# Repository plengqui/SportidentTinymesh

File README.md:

# Sportident online control using Tinymesh 169Mhz radio
A forest-optimized, reliable mesh radio for Sportident with up to 1,5km per hop.
This document introduces the project idea and product vision on a high level.
# Project context and background
In orienteering and other outdoor sports, the [Sportident](https://www.sportident.com/) system is often used to electronically register when a participant passes a checkpoint. One drawback of Sportident is that the checkpoint pass time registrations cannot be read out until the participant has finished the course. In order to make sports using the Sportident system more exciting for the audience, there is a need for real-time communication from the checkpoints to the competition administration at the arena. A number of solutions already exist for this, such as the excellent [Radio Online Control](http://olresultat.se/), current loop signaling over military [telephone wire](http://hem.bredband.net/sunjo/index.htm), [jSh Radio](http://radio.jsh.de/), etc. While they each have their advantages, most solutions are a bit bulky which makes it burdensome to deploy more than a couple of online checkpoints in each race. For solutions that rely on mobile data networks, there is also the risk at big competitions that the network becomes overloaded on competition day by the large number of runners and viewers appearing on the arena, which is typically a location where mobile networks are not dimensioned for such high load. 
# Product vision
This project aims to produce a neat lightweight radio solution that is easy to deploy in forest conditions, while being very reliable in terms of delivering 100% of punches to the arena in all possible weather conditions. The finished product is a radio unit - a small box about the size of a fist - which is directly attached to a flexible 130 cm roll-up antenna. The antenna + radio unit can hang from a tree anywhere within 8m from the Sportident units at the control. No cabling is needed on the ground. No calibration of directional antennas is needed.
About 10 radio units including antennas can be carried in a backpack and easily deployed by one person with very limited technical knowledge. 
# Technologies used
## Tinymesh
The radio units communicate using a widely used and well supported mesh radio protocol from Radiocrafts called Tinymesh. They use the 169 MHz band, which implies wavelengths of almost 2 meters. Thus they have very good propagation even through dense and wet forest. Distances of 1,5 km per hop have been tested with continuous operation through hilly forest with 500mW effect and Slim Jim antennas. Tinymesh is a self-configuring, self-healing, monitorable mesh technology, implemented in a small surface-mounted component containing both transceiver and protocol logic.
Nodes in a Tinymesh network can be of two types: Router or Gateway. There is only one Gateway per network. All serial data sent from Rounters are automatically routed to the Gateway.
The [Tinymesh datasheet](docs/RCxxxxHP-TM_Data_Sheet.pdf) from Radiocrafts contains everything we need to know in this project, from an overview of the solution to detailed explanation of the protocol and packet formats. I have highlighted the parts of the datasheet that are relevant to this project and added some annotations. The specific module we use is RC1701(HP)-TM, whose default operating frequency is 169.40625 MHz with max effect of 500mW.
This radio band is unlicensed in most european countries, including [Sweden](https://www.pts.se/sv/Bransch/Radio/Radiotillstand/Undantag-fran-tillstandsplikt/):
>88 § 169,400–169,475 MHz: Radiosändare för ospecificerat tillämpningsområde. Högsta effekt: 500 mW e.r.p. Kanaldelning: Upp till 50 kHz. Sändningscykel: < 1 %

>89 § 169,400–169,475 MHz: Radiosändare för mätutrustning. Högsta effekt: 500 mW e.r.p. Kanaldelning: Upp till 50 kHz. Sändningscykel: < 10 %.

## Slim Jim antenna

The Slim Jim antenna is perfect for this application, being easy to transport rolled up, and quick to deploy by just hanging it from a tree nearby, up to 8m from the Sportident station. The antenna is 130 cm long, and the small Radio Unit box can be attached diretly at the lower end of the antenna. 

## Sportident Short Range Radio (SRR)
The Sportident units at the control are [SRR](https://www.sportident.com/images/PDF/1_si_base_products/8_si-radio/SRR-Kit/SPORTident_SRR_en.pdf) stations, which communicate with the radio unit via a proprietary Sportident radio protocol on the 2,4 GHz band. 

# System design and architecture

Apart from the standard off-the-shelf Sportident SRR stations, the system consists of two main parts:
1. The neat field-deployable radio unit, of which there will be one per checkpoint. The radio unit receives punch data from the Sportident stations over SRR, and retransmits it over the 169 MHz Tinymesh network. The Tinymesh network architecture has one central Gateway node to which all data is sent.
2. The Gateway, consisting of a Tinymesh radio module directly connected to a PC running our custom python Gateway Application which parses the Tinymesh packets and forwards the Sportident punch data to the competition administration system. Integrates with competition administration system like OLA or MeOS using the SIRAP protocol.
There is pretty comprehensive documentation of the Gateway Application code available in its [README](https://github.com/plengqui/GatewayApplication/blob/master/README.md).

## The radio unit

The radio unit is a small box of electronics with only one external connector for the SlimJim roll-up antenna. As mentioned, the antenna and the radio unit box are meant to hang from a tree nearby the checkpoint. Inside the box, there is a custom made printed
circuit board (PCB) with:
- a Sportident SRR receiver chip, which listens to 2,4GHz for punch packets and sends them out over UART serial. 
- A Teensy-LC (a cheap small Arduino style microcontroller) receives the punch data, creates a Tinymesh data packet and passes it on to the Tinymesh radio module, again over UART serial. 
- The Tinymesh radio module sends the data packet with the punch data out on the Tinymesh network which forwards it to the gateway Tinymesh module. The model number of Tinymesh used is RC1701(HP)-TM.
- The Teensy-LC microcontroller also buffers punches if the Tinymesh module should be busy or waiting for a free timeslot on the frequency. It also sends monitoring packets every 10 seconds so that the central pc application can allways know all radio units are up and connected.
- Battery: 18650 Lithium cells and a voltage regulator, serving the 3,3V needed by Tinymesh and Teensy-LC.
- Antenna for 169MHz with SMA male connector. Either a SlimJim, which you can [build](https://www.essexham.co.uk/slim-jim) or [buy](http://www.2wayelectronix.com/). Or a "normal" whip antenna like [this one](https://www.digikey.se/product-detail/en/taoglas-limited/FW.80.SMA.M/931-1195-ND/3664652). SlimJim is best for real-world application in the woods. A whip is good for lab and test.

## The Gateway
This is the central part of the system that collects all punches from all controls and forwards them to the competition administration system. It also monitors the health and connectivity status of all controls. The Gateway is a Tinymesh module configured as the gateway of the mesh network, connected with simple serial to a PC running the Gateway Application. 
To save time, I have so far used the Tinymesh Demo Kit (RC1701HP-TM-DK) which has a USB connection and appears as a logical COM port in the PC. However, it should be quite easy to use a Radio Unit as gateway (see TODOs below).

The Gateway Application is written in Python 3 and consists of two parts: a small simple script running as a separate process which just listens to the COM port of the Tinymesh gateway and writes every received packet to a store-and-forward queue. This queue is read by the main python application which parses each Tinymesh packet on the queue and handles it. Packets that are punch registrations are sent to the competition administration system using the SIRAP protocol. The application also has a GUI that shows status and health of each control, and any alarms:

The Github repository for the gateway application is [here](https://github.com/plengqui/GatewayApplication/).

# Project progress and status

This has been completed so far:
1.	Selected and tested radio, frequency and antenna solution. 1,5km hop reached with rollup slim-jim antenna using the Tinymesh RC1701(HP)-TM with 500 mW effect on the license free 169 MHz ISM band. 
2.	Verified Tinymesh mesh radio network in real Orienteering competition using Tinymesh developer kits in July 2016. Two controls and one gateway.  This worked great. All punches were received online. 
3.	Written pc application in python to receive and parse Tinymesh and Sportident packets. Use Tinymesh in packet mode, to monitor the health of the mesh network using the packet metadata and the various command packets of Tinymesh. This is referred to as the Gateway Application above. 
4.	Designed and built a neat field-deployable Radio Unit with custom made printed circuit board (PCB), surface-mounted Tinymesh chip, battery, and a Teensy (a cheap small Arduino style microcontroller) for control logic.
5.	Written and tested Teensy code to simulate Sportident punches and send them to the Tinymesh radio module. Tested connectivity from the Teensy to the python application running on the PC, over Tinymesh radio. Load tested with 3 simulated punches per second, continuously for 2 hours.
6.  Got the Sportident SRR chip working with the Radio Unit. So now full integration from Sportident punch to Gateway Application is done. Rudimentary support for flow control reading the Tinymesh CTS status before and after sending each packet. So far relies on Teensys serial buffers for buffering.
7. Implemented SIRAP protocol in the Python Gateway application. Tested with OLA competition administration system. Now we have a complete end-to-end system!

# Getting Started
List of needed components for the Radio Unit, how to get them and putting it all together is [here](./RadioUnit/README.md).

When the Radio Unit is built, you just need to:
1. connect the antenna
2. upload the sketch teensy-sportident-srr.ino to the Teensy using the [Arduino IDE](https://www.arduino.cc/en/Main/Software)
3. connect a usb power source to the micro usb of the Teensy.
4. attach the gateway demokit module to the pc.
5. start the [Gateway Application](https://github.com/plengqui/GatewayApplication/blob/master/README.md) on the PC 
6. try some punches in the SRR station!

Any problems? Just drop me an email at ```per (kanelbulle) lengquist.se```

# TODO: ideas for further improvement
-	Build more Radio Units and test in more real orienteering events. Please drop me an email if you know where to borrow more SRR master stations.
- Implement support for RS232 Sportident stations. Support in Teensy for multiple stations (multiple serial ports in).
- Select a good solution for physical enclosure. Also decide battery solution: powerbank or 18650 LiIon cells. 
- Invent a way for the person deploying the Radio Units in the forest to get verification that each deployed online control works end-to-end. Perhaps by the Gateway Application publishing its status logs on a web page or [Slack](https://api.slack.com/).
- Use a Radio Unit as Gateway instead of the rather expensive Demo Kit: Write a Teensy program to configure the Tinymesh module as a gateway. Then use a [simple Teensy program](https://github.com/arduino/Arduino/blob/master/build/shared/examples/04.Communication/MultiSerial/MultiSerial.ino) to pipe through serial data between USB serial and the Tinymesh in normal operation.

Any suggestions or feedback? Just drop me an email at ```per (kanelbulle) lengquist.se```

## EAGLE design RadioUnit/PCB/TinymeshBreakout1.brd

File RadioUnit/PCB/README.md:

This directory contains design files for the Printed Circuit Board (PCB) on which the components are soldered. 
The Tinymesh module is surface-mount soldered, while the other components are traditional through-hole. 

The board design has no fixed copper wiring between the components. This makes it possible to use for experimentation and test different designs without printing new PCBs.

The files are created using [Eagle](https://www.autodesk.com/products/eagle/free-download).
I ordered the boards from [Eurocircuits](https://www.eurocircuits.com/blog/NAKED-proto/). 
5 boards cost 48,5 EUR incl VAT and shipping. See order details in the file [E855315.pdf](./E855315.pdf). If you refer to that, or maybe "PCB B0826634", and they have saved my specification and design, you may be able to order new copies the exact same PCB that I got. I can confirm it is suitable for the components I used including the Tinymesh module. 

Here is a good video tutorial (from the great Collin's Lab) on hand solering a surface mount component with QFN package like the Tinymesh module:
https://youtu.be/QzoPxvIM2qE?t=349

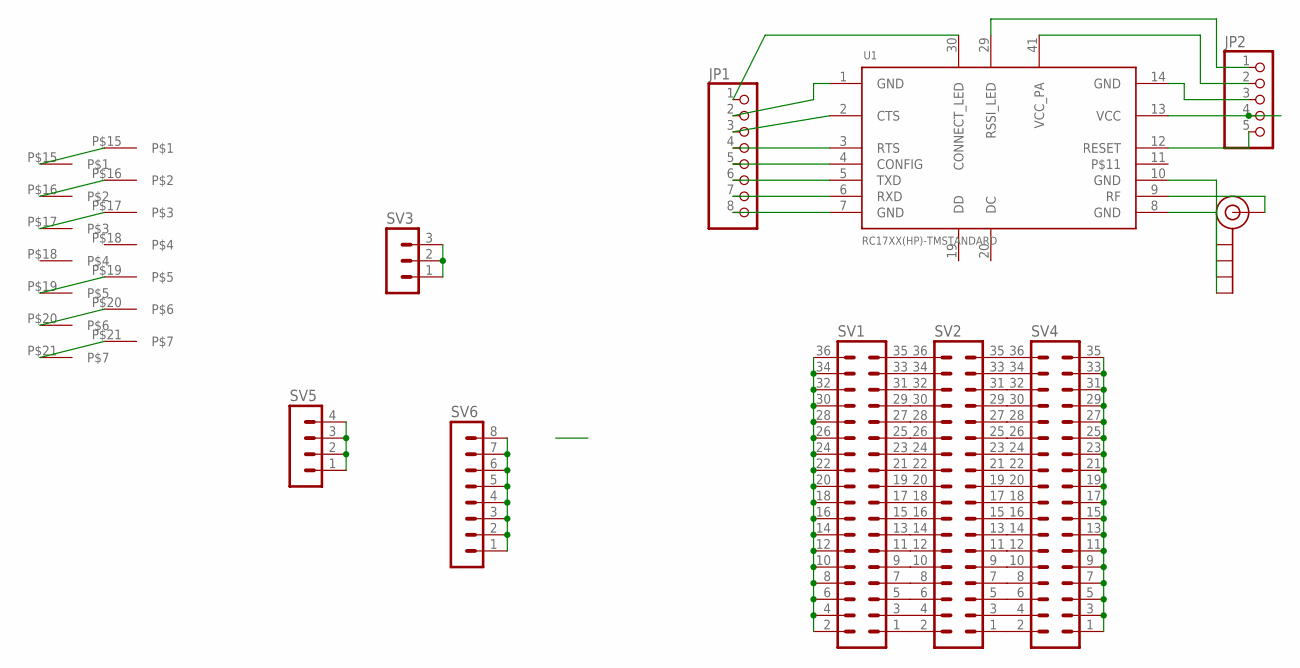
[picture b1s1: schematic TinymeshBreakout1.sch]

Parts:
J$1: SMA_EDGE; SMA-EDGE
JP1: PINHD-1X8; 1X08
JP2: PINHD-1X5; 1X05
SV1, SV2, SV4: MA18-2
SV3: MA03-1
SV5: MA04-1
SV6: MA08-1
U1: RC17XX(HP)-TMSTANDARD; RC17XX(HP)-TM
U$1, U$2: OEMSRR

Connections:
GND: J$1.GND@2 (GND), J$1.GND@3 (GND), JP1.2, JP2.3, SV1.2, SV1.4, SV1.6, SV1.8, SV1.10, SV1.12, SV1.14, SV1.16, SV1.18, SV1.20, SV1.22, SV1.24, SV1.26, SV1.28, SV1.30, SV1.32, SV1.34, SV1.36, U1.1 (GND), U1.8 (GND), U1.10 (GND), U1.14 (GND)
unnamed: SV1.1, SV2.2
unnamed: SV1.3, SV2.4
unnamed: J$1.SIG (SIGNAL), U1.9 (RF)
unnamed: JP2.5, U1.12 (RESET)
unnamed: SV1.5, SV2.6
unnamed: SV1.7, SV2.8
unnamed: SV1.9, SV2.10
unnamed: SV1.11, SV2.12
unnamed: JP1.7, U1.6 (RXD)
unnamed: JP1.6, U1.5 (TXD)
unnamed: JP1.5, U1.4 (CONFIG)
unnamed: JP1.4, U1.3 (RTS)
unnamed: JP1.3, U1.2 (CTS)
unnamed: SV1.13, SV2.14
unnamed: JP1.1, U1.30 (CONNECT_LED)
unnamed: JP2.1, U1.29 (RSSI_LED)
unnamed: SV1.15, SV2.16
unnamed: SV1.17, SV2.18
unnamed: SV1.19, SV2.20
unnamed: SV1.21, SV2.22
unnamed: SV1.23, SV2.24
unnamed: SV1.25, SV2.26
unnamed: SV1.27, SV2.28
unnamed: SV1.29, SV2.30
unnamed: SV1.31, SV2.32
unnamed: SV1.33, SV2.34
unnamed: SV1.35, SV2.36
unnamed: SV2.1, SV4.2
unnamed: SV2.3, SV4.4
unnamed: SV2.5, SV4.6
unnamed: SV2.7, SV4.8
unnamed: U$1.P$15, U$2.P$15
unnamed: JP2.4, U1.13 (VCC)
unnamed: JP1.8, U1.7 (GND)
unnamed: SV2.9, SV4.10
unnamed: SV2.11, SV4.12
unnamed: SV2.13, SV4.14
unnamed: SV2.15, SV4.16
unnamed: SV2.17, SV4.18
unnamed: SV2.19, SV4.20
unnamed: SV2.21, SV4.22
unnamed: SV2.23, SV4.24
unnamed: SV2.25, SV4.26
unnamed: SV2.27, SV4.28
unnamed: SV2.29, SV4.30
unnamed: SV2.31, SV4.32
unnamed: SV2.33, SV4.34
unnamed: SV2.35, SV4.36
unnamed: U$1.P$16, U$2.P$16
unnamed: SV4.1, SV4.3, SV4.5, SV4.7, SV4.9, SV4.11, SV4.13, SV4.15, SV4.17, SV4.19, SV4.21, SV4.23, SV4.25, SV4.27, SV4.29, SV4.31, SV4.33, SV4.35
unnamed: U$1.P$17, U$2.P$17
unnamed: U$1.P$19, U$2.P$19
unnamed: U$1.P$20, U$2.P$20
unnamed: U$1.P$21, U$2.P$21
unnamed: SV5.1, SV5.2, SV5.3, SV5.4
unnamed: SV6.1, SV6.2, SV6.3, SV6.4, SV6.5, SV6.6, SV6.7, SV6.8
unnamed: SV3.1, SV3.2, SV3.3
VCC: JP2.2, U1.41 (VCC_PA)

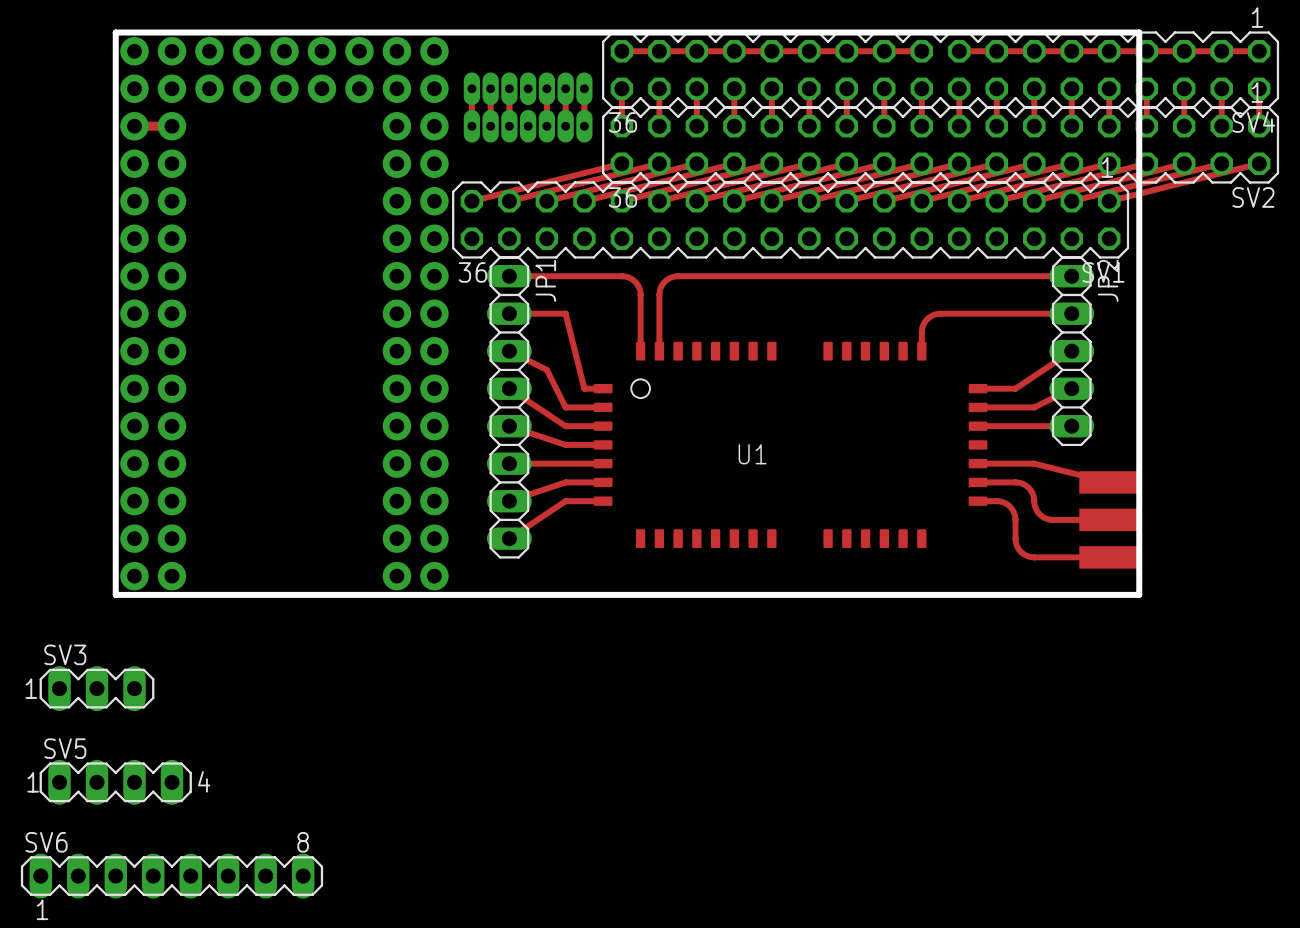
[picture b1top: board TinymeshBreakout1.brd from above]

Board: 2 copper layers, 12 parts (0 on the bottom side), 59 nets.

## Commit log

2017-10-13 Set theme jekyll-theme-cayman
2017-10-13 First version of README
2017-10-13 Added spaces
2017-10-14 Added architecture and design section
2017-10-15 Diagram with overview of the system architecture.
2017-10-15 Try to embed an image...
2017-10-17 removed unneeded image file
2017-10-17 moved image file to docs
2017-10-17 Added PCB, Teensy Scetches, and some photos.
2017-10-17 updated readme with pictures
2017-10-21 GUI screenshot
2017-10-21 Removed queue from picture to make it simpler
2017-10-23 Updated links to GatewayApplication since I changed the name of its repository from tmsi to GatewayApplication.
2017-10-27 Photo that shows pinout of a SRR-OEM board.
2017-10-29 teensy scetch
2017-10-31 Added jSh Radio to list of similar projects.
2017-10-31 Highlighted relevant parts.
    Highlighted the parts that are most relevant to this project, and added a few annotations.
2017-11-01 Sportident CRC for Arduino
2017-11-01 removed files with space in the name
2017-11-01 Makes Teensy simulate Sportident punches and send to Tinymesh
2017-11-02 Sportident programmers guide, with relevant text highlighted.
2017-11-02 Bill of materials
2017-11-02 Rename NeededComponents.md to RadioUnit/NeededComponents.md
2017-11-03 Order details from Eurocircuits
2017-11-03 Added how to put it together
2017-11-03 Tinymesh pinout
2017-11-03 Rename NeededComponents.md to BuildingTheRadioUnit.md
2017-11-03 Rename BuildingTheRadioUnit.md to README.md
2017-11-04 Implemented support for SIRAP
2017-11-08 Remove waiting for serial monitor. So it can be used standalone.
2017-11-09 Prettier indent
2017-11-16 Added info and sketch about configuration.
2017-11-16 Fixed indentation

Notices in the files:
parts and their libraries:
SparkFun-Connectors: Licensing: Creative Commons ShareAlike 4.0 International - https://creativecommons.org/licenses/by-sa/4.0
